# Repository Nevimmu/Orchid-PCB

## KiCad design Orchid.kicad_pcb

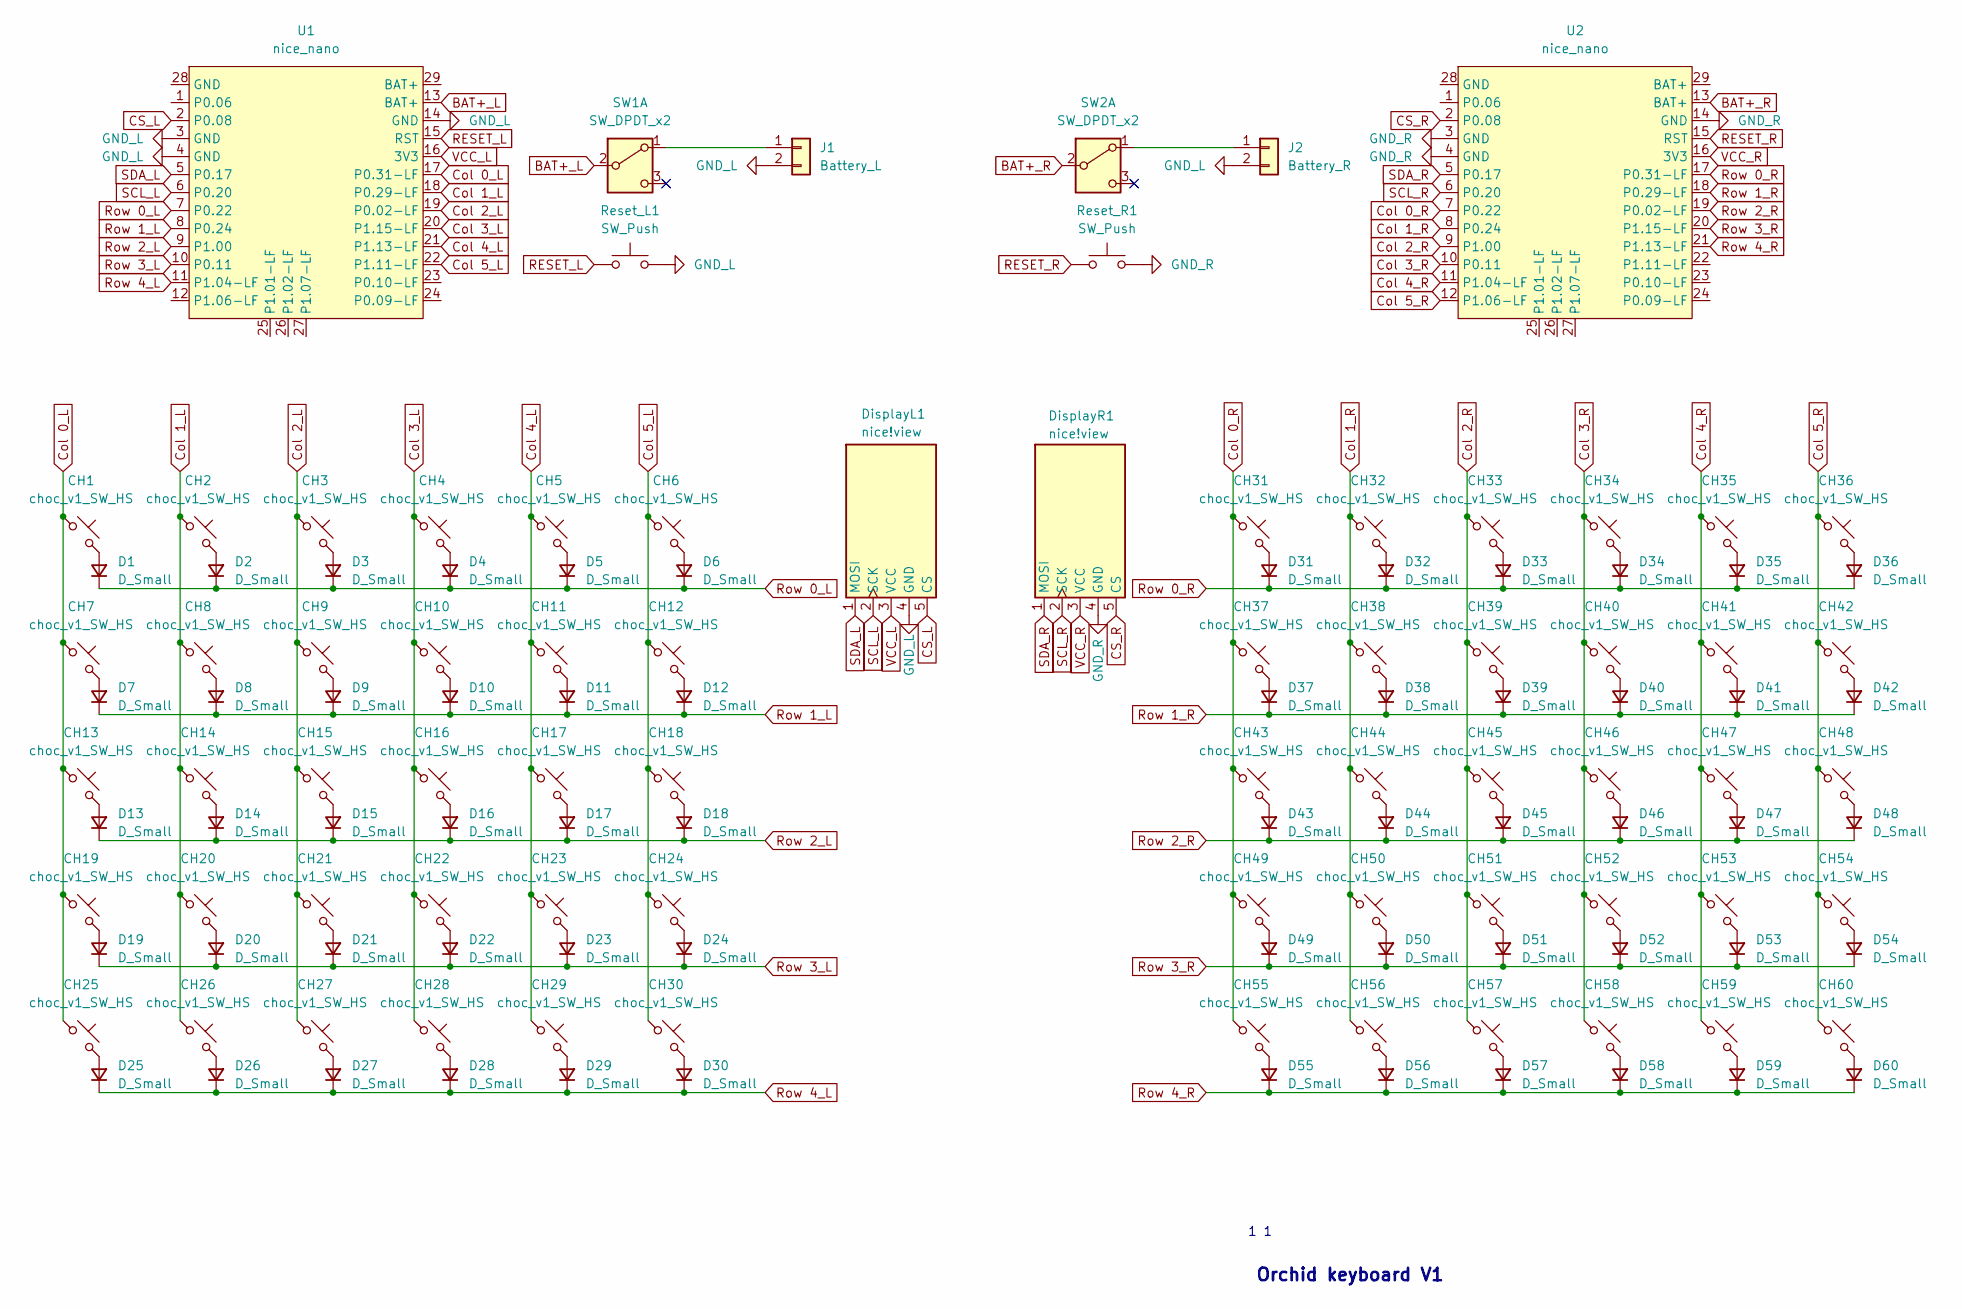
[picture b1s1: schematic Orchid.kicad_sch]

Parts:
CH1, CH2, CH3, CH4, CH5, CH6, CH7, CH8, CH9, CH10, CH11, CH12, CH13, CH14, CH15, CH16, CH17, CH18, CH19, CH20, CH21, CH22, CH23, CH24, CH25, CH26, CH27, CH28, CH29, CH30, CH31, CH32, CH33, CH34, CH35, CH36, CH37, CH38, CH39, CH40, CH41, CH42, CH43, CH44, CH45, CH46, CH47, CH48, CH49, CH50, CH51, CH52, CH53, CH54, CH55, CH56, CH57, CH58, CH59, CH60: choc_v1_SW_HS; SW_choc_v1_HS_CPG135001S30_1u
D1, D2, D3, D4, D5, D6, D7, D8, D9, D10, D11, D12, D13, D14, D15, D16, D17, D18, D19, D20, D21, D22, D23, D24, D25, D26, D27, D28, D29, D30, D31, D32, D33, D34, D35, D36, D37, D38, D39, D40, D41, D42, D43, D44, D45, D46, D47, D48, D49, D50, D51, D52, D53, D54, D55, D56, D57, D58, D59, D60: D_Small; D_SOD-123-Pretty
DisplayL1: nice!view; nice_view
DisplayR1: nice!view; nice_view
J1: Battery_L; CON_JST_ACH_BM02B
J2: Battery_R; CON_JST_ACH_BM02B
Reset_L1: SW_Push; Reset_Pretty
Reset_R1: SW_Push; Reset_Pretty
SW1, SW2: SW_DPDT_x2; SW_SKHLLCA010
U1, U2: nice_nano; nice_nano_AH_USBup

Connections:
BAT+_L: SW1.2 (B), U1.13 (BAT+)
BAT+_R: SW2.2 (B), U2.13 (BAT+)
CS_L: DisplayL1.5 (CS), U1.2 (P0.08)
CS_R: DisplayR1.5 (CS), U2.2 (P0.08)
Col 0_L: CH1.1, CH7.1, CH13.1, CH19.1, CH25.1, U1.17 (P0.31-LF)
Col 0_R: CH31.1, CH37.1, CH43.1, CH49.1, CH55.1, U2.7 (P0.22)
Col 1_L: CH2.1, CH8.1, CH14.1, CH20.1, CH26.1, U1.18 (P0.29-LF)
Col 1_R: CH32.1, CH38.1, CH44.1, CH50.1, CH56.1, U2.8 (P0.24)
Col 2_L: CH3.1, CH9.1, CH15.1, CH21.1, CH27.1, U1.19 (P0.02-LF)
Col 2_R: CH33.1, CH39.1, CH45.1, CH51.1, CH57.1, U2.9 (P1.00)
Col 3_L: CH4.1, CH10.1, CH16.1, CH22.1, CH28.1, U1.20 (P1.15-LF)
Col 3_R: CH34.1, CH40.1, CH46.1, CH52.1, CH58.1, U2.10 (P0.11)
Col 4_L: CH5.1, CH11.1, CH17.1, CH23.1, CH29.1, U1.21 (P1.13-LF)
Col 4_R: CH35.1, CH41.1, CH47.1, CH53.1, CH59.1, U2.11 (P1.04-LF)
Col 5_L: CH6.1, CH12.1, CH18.1, CH24.1, CH30.1, U1.22 (P1.11-LF)
Col 5_R: CH36.1, CH42.1, CH48.1, CH54.1, CH60.1, U2.12 (P1.06-LF)
GND_L: DisplayL1.4 (GND), J1.2, J2.2, Reset_L1.2, U1.3 (GND), U1.4 (GND), U1.14 (GND)
GND_R: DisplayR1.4 (GND), Reset_R1.2, U2.3 (GND), U2.4 (GND), U2.14 (GND)
unnamed: CH1.2, D1.2 (A)
unnamed: CH2.2, D2.2 (A)
unnamed: CH3.2, D3.2 (A)
unnamed: CH4.2, D4.2 (A)
unnamed: CH5.2, D5.2 (A)
unnamed: CH6.2, D6.2 (A)
unnamed: CH7.2, D7.2 (A)
unnamed: CH8.2, D8.2 (A)
unnamed: CH9.2, D9.2 (A)
unnamed: CH10.2, D10.2 (A)
unnamed: CH11.2, D11.2 (A)
unnamed: CH12.2, D12.2 (A)
unnamed: CH13.2, D13.2 (A)
unnamed: CH14.2, D14.2 (A)
unnamed: CH15.2, D15.2 (A)
unnamed: CH16.2, D16.2 (A)
unnamed: CH17.2, D17.2 (A)
unnamed: CH18.2, D18.2 (A)
unnamed: CH19.2, D19.2 (A)
unnamed: CH20.2, D20.2 (A)
unnamed: CH21.2, D21.2 (A)
unnamed: CH22.2, D22.2 (A)
unnamed: CH23.2, D23.2 (A)
unnamed: CH24.2, D24.2 (A)
unnamed: CH25.2, D25.2 (A)
unnamed: CH26.2, D26.2 (A)
unnamed: CH27.2, D27.2 (A)
unnamed: CH28.2, D28.2 (A)
unnamed: CH29.2, D29.2 (A)
unnamed: CH30.2, D30.2 (A)
unnamed: CH31.2, D31.2 (A)
unnamed: CH32.2, D32.2 (A)
unnamed: CH33.2, D33.2 (A)
unnamed: CH34.2, D34.2 (A)
unnamed: CH35.2, D35.2 (A)
unnamed: CH36.2, D36.2 (A)
unnamed: CH37.2, D37.2 (A)
unnamed: CH38.2, D38.2 (A)
unnamed: CH39.2, D39.2 (A)
unnamed: CH40.2, D40.2 (A)
unnamed: CH41.2, D41.2 (A)
unnamed: CH42.2, D42.2 (A)
unnamed: CH43.2, D43.2 (A)
unnamed: CH44.2, D44.2 (A)
unnamed: CH45.2, D45.2 (A)
unnamed: CH46.2, D46.2 (A)
unnamed: CH47.2, D47.2 (A)
unnamed: CH48.2, D48.2 (A)
unnamed: CH49.2, D49.2 (A)
unnamed: CH50.2, D50.2 (A)
unnamed: CH51.2, D51.2 (A)
unnamed: CH52.2, D52.2 (A)
unnamed: CH53.2, D53.2 (A)
unnamed: CH54.2, D54.2 (A)
unnamed: CH55.2, D55.2 (A)
unnamed: CH56.2, D56.2 (A)
unnamed: CH57.2, D57.2 (A)
unnamed: CH58.2, D58.2 (A)
unnamed: CH59.2, D59.2 (A)
unnamed: CH60.2, D60.2 (A)
unnamed: J1.1, SW1.1 (A)
unnamed: J2.1, SW2.1 (A)
RESET_L: Reset_L1.1, U1.15 (RST)
RESET_R: Reset_R1.1, U2.15 (RST)
Row 0_L: D1.1 (K), D2.1 (K), D3.1 (K), D4.1 (K), D5.1 (K), D6.1 (K), U1.7 (P0.22)
Row 0_R: D31.1 (K), D32.1 (K), D33.1 (K), D34.1 (K), D35.1 (K), D36.1 (K), U2.17 (P0.31-LF)
Row 1_L: D7.1 (K), D8.1 (K), D9.1 (K), D10.1 (K), D11.1 (K), D12.1 (K), U1.8 (P0.24)
Row 1_R: D37.1 (K), D38.1 (K), D39.1 (K), D40.1 (K), D41.1 (K), D42.1 (K), U2.18 (P0.29-LF)
Row 2_L: D13.1 (K), D14.1 (K), D15.1 (K), D16.1 (K), D17.1 (K), D18.1 (K), U1.9 (P1.00)
Row 2_R: D43.1 (K), D44.1 (K), D45.1 (K), D46.1 (K), D47.1 (K), D48.1 (K), U2.19 (P0.02-LF)
Row 3_L: D19.1 (K), D20.1 (K), D21.1 (K), D22.1 (K), D23.1 (K), D24.1 (K), U1.10 (P0.11)
Row 3_R: D49.1 (K), D50.1 (K), D51.1 (K), D52.1 (K), D53.1 (K), D54.1 (K), U2.20 (P1.15-LF)
Row 4_L: D25.1 (K), D26.1 (K), D27.1 (K), D28.1 (K), D29.1 (K), D30.1 (K), U1.11 (P1.04-LF)
Row 4_R: D55.1 (K), D56.1 (K), D57.1 (K), D58.1 (K), D59.1 (K), D60.1 (K), U2.21 (P1.13-LF)
SCL_L: DisplayL1.2 (SCK), U1.6 (P0.20)
SCL_R: DisplayR1.2 (SCK), U2.6 (P0.20)
SDA_L: DisplayL1.1 (MOSI), U1.5 (P0.17)
SDA_R: DisplayR1.1 (MOSI), U2.5 (P0.17)
VCC_L: DisplayL1.3 (VCC), U1.16 (3V3)
VCC_R: DisplayR1.3 (VCC), U2.16 (3V3)

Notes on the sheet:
1 1
Orchid keyboard V1

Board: 2 copper layers, 130 parts (60 on the bottom side), 98 nets, no tracks yet.

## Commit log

2024-12-03 First commit.
2024-12-03 Add submodeules.
2024-12-17 Removed MX_V2 submodule.
2024-12-17 Add footprint lib.
2024-12-17 Created the grid.
2024-12-18 Added components.
2024-12-18 Completed the diagram.
2024-12-23 Added niceview.
2024-12-23 vcc.
2024-12-23 Assigned footprints.
2024-12-23 Added title.
2025-01-07 added matrix to pcb
